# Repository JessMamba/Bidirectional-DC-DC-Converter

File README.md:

# Three-Stage Cubic Bidirectional DC-DC Converter for Renewable Energy & Battery Storage Systems

A high-gain, non-isolated, high-efficiency **Three-Stage Cubic Bidirectional DC-DC Converter** designed for renewable energy systems, battery energy storage systems (BESS), and electric vehicle (EV) microgrid interfaces (V2G/G2V). 

This repository contains full theoretical derivations (CCM/DCM), circuit parameter calculations, 3D MATLAB optimization surface scripts, mode-dependent closed-loop PID controller designs, PSCAD simulation models, and KiCad PCB designs/Gerber files with hardware prototype implementation details.

---

## 📌 Table of Contents
- [1. Executive Summary](#1-executive-summary)
- [2. Key Features & Specifications](#2-key-features--specifications)
- [3. Converter Topology & Operating Principles](#3-converter-topology--operating-principles)
  - [3.1 Step-Up (Boost) Mode](#31-step-up-boost-mode)
  - [3.2 Step-Down (Buck) Mode](#32-step-down-buck-mode)
- [4. Mathematical Modeling & Component Calculations](#4-mathematical-modeling--component-calculations)
  - [4.1 Voltage Gain Expressions](#41-voltage-gain-expressions)
  - [4.2 Inductor & Capacitor Dimensioning](#42-inductor--capacitor-dimensioning)
  - [4.3 Switch Voltage and Current Stress Analysis](#43-switch-voltage-and-current-stress-analysis)
  - [4.4 Comparative Analysis](#44-comparative-analysis)
- [5. Mode-Dependent Closed-Loop PID Controller Design](#5-mode-dependent-closed-loop-pid-controller-design)
  - [5.1 Buck Mode Controller](#51-buck-mode-controller)
  - [5.2 Boost Mode Controller](#52-boost-mode-controller)
  - [5.3 MATLAB Closed-Loop Verification](#53-matlab-closed-loop-verification)
- [6. PSCAD Simulation & Results](#6-pscad-simulation--results)
- [7. Hardware Bill of Materials (BOM)](#7-hardware-bill-of-materials-bom)
- [8. PCB Design & Hardware Implementation](#8-pcb-design--hardware-implementation)
- [9. Repository Structure](#9-repository-structure)
- [10. References](#10-references)

---

## 1. Executive Summary

Conventional boost and buck converters suffer from extreme duty cycle requirements, excessive semiconductor stress, and sharp efficiency degradation when operating at large voltage conversion ratios. To eliminate these constraints, this project proposes a **Three-Stage Cubic Bidirectional DC-DC Converter**. 

By leveraging a cubic voltage transfer ratio ($M_{	ext{Boost}} = rac{1}{(1-D)^3}$ and $M_{	ext{Buck}} = D^3$), the converter achieves a wide voltage conversion range (**24V DC $\leftrightarrow$ 300V DC**) at moderate duty cycles ($D_{	ext{Boost}} = 0.57$, $D_{	ext{Buck}} = 0.43$) while maintaining lower voltage and current stresses on power MOSFETs. The topology utilizes **6 MOSFET switches, 4 capacitors, and 3 inductors**, achieving a calculated peak efficiency of **94.16%** due to reduced switching losses (only 1 or 2 switches actively triggered in each sub-interval).

---

## 2. Key Features & Specifications

| Parameter | Symbol | Nominal Value | Unit |
| :--- | :--- | :--- | :--- |
| **Rated Power** | $P_{o}$ | **900** | W |
| **Low Voltage Side (LV)** | $V_{LV}$ | **24** | V |
| **High Voltage Side (HV)** | $V_{HV}$ | **300** | V |
| **Switching Frequency** | $f_s$ | **50** | kHz |
| **Peak Efficiency** | $\eta_{	ext{peak}}$ | **94.16** | % |
| **Boost Duty Cycle ($24	ext{V}	o300	ext{V}$)** | $D_{	ext{boost}}$ | **0.5703** | - |
| **Buck Duty Cycle ($300	ext{V}	o24	ext{V}$)** | $D_{	ext{buck}}$ | **0.4305** | - |
| **Maximum Duty Cycle Limit** | $D_{	ext{max}}$ | **0.90** | - |
| **Ground Topology** | - | **Common Ground** | - |

---

## 3. Converter Topology & Operating Principles

The converter consists of three energy storage inductors ($L_1, L_2, L_3$), two intermediate energy transfer capacitors ($C_1, C_2$), input/output filtering capacitors ($C_L, C_H$), and 6 MOSFET switches ($S_1, S_2, S_3, S_4, S_5, S_6$) configured for bidirectional power flow.

```
                  +--------------------[ S1 ]-------------------+
                  |                                             |
                  |          S2                     S3          |
  [LV Input] -----+---(L1)---[--]---+---(L2)---[--]----+        |
  (24V DC)        |                 |                  |        |
                  |                --- C1             --- C2    |
                 --- CL            ---                ---       |
                 ---                |                  |        |
                  |                GND         [S4]----+---(L3)-+---[S6]---+--- [HV Output]
                  |                             |               |          |    (300V DC)
                  |                            GND             [S5]       --- CH
                  |                                             |         ---
                  +---------------------------------------------+----------+--- GND
```

### 3.1 Step-Up (Boost) Mode
Energy flows from Low Voltage ($V_{LV} = 24	ext{V}$) to High Voltage ($V_{HV} = 300	ext{V}$).
- **State 1 ($0 \le t < D T_s$):** Switches $S_1, S_4, S_5$ are ON; body diodes $D_1, D_2, D_3$ are reverse-biased. $L_1$ is magnetized by $V_{LV}$, while $L_2$ and $L_3$ are magnetized by intermediate capacitors $C_1$ and $C_2$. All inductor currents increase linearly.
- **State 2 ($D T_s \le t < T_s$):** Switches $S_1, S_4, S_5$ are OFF; body diodes $D_1, D_2, D_3$ conduct. Stored energy is transferred forward: $L_1$ charges $C_1$, $L_2$ charges $C_2$, and $L_3$ feeds the HV load and output filtering capacitor $C_H$.

### 3.2 Step-Down (Buck) Mode
Energy flows from High Voltage ($V_{HV} = 300	ext{V}$) to Low Voltage ($V_{LV} = 24	ext{V}$).
- **State 1 ($0 \le t < D T_s$):** Switches $S_2, S_3, S_6$ are ON. $L_3$ is energized by $V_{HV}$, and $L_2, L_1$ are energized by intermediate capacitors $C_2, C_1$. Inductor currents ramp up linearly.
- **State 2 ($D T_s \le t < T_s$):** Switches $S_2, S_3, S_6$ are OFF; body diodes $D_1, D_4, D_5$ conduct. Energy is demagnetized toward the LV side: $L_3 	o C_2$, $L_2 	o C_1$, and $L_1 	o R_{	ext{load}}$ (LV side).

---

## 4. Mathematical Modeling & Component Calculations

### 4.1 Voltage Gain Expressions

#### Continuous Conduction Mode (CCM)
- **Intermediate Capacitor Voltages (Boost):**
  $$V_{C1} = rac{V_{LV}}{1-D}, \quad V_{C2} = rac{V_{LV}}{(1-D)^2}$$
- **Intermediate Capacitor Voltages (Buck):**
  $$V_{C2} = D \cdot V_{HV}, \quad V_{C1} = D^2 \cdot V_{HV}$$
- **Cubic Voltage Transfer Ratio (VTR):**
  $$M_{	ext{CCM, Step-Up}} = rac{V_{HV}}{V_{LV}} = rac{1}{(1-D)^3}$$
  $$M_{	ext{CCM, Step-Down}} = rac{V_{LV}}{V_{HV}} = D^3$$

#### Discontinuous Conduction Mode (DCM)
- **Step-Up Mode DCM Gain:**
  $$M_{	ext{DCM, Step-Up}} = rac{V_{HV}}{V_{LV}} = rac{(D+D_1)(D+D_2)(D+D_3)}{D_1 (D D_2 + D_2 D_3 - D D_3)}$$
- **Step-Down Mode DCM Gain:**
  $$M_{	ext{DCM, Step-Down}} = rac{V_{LV}}{V_{HV}} = rac{D^2 (D + D_3 - D_2)}{(D + D_1)(D + D_2)(D + D_3)}$$

### 4.2 Inductor & Capacitor Dimensioning

Inductances and capacitances are dimensioned analytically to ensure robust CCM operation with current and voltage ripple $<1\%$:

$$L_1 \ge rac{D_{	ext{boost}} V_{LV}}{\Delta i_{L1} f_s}, \quad L_2 \ge rac{D_{	ext{boost}} V_{LV}}{(1-D_{	ext{boost}}) \Delta i_{L2} f_s}, \quad L_3 \ge rac{D_{	ext{boost}} V_{LV}}{(1-D_{	ext{boost}})^2 \Delta i_{L3} f_s}$$

| Component | Minimum Calculated (Boost) | Minimum Calculated (Buck) | Selected Hardware Value |
| :--- | :--- | :--- | :--- |
| **Inductor $L_1$** | $0.3898	ext{ mH}$ | $0.2282	ext{ mH}$ | **$330\ \mu	ext{H}$ / High Current Toroid** |
| **Inductor $L_2$** | $0.7418	ext{ mH}$ | $0.5940	ext{ mH}$ | **$330\ \mu	ext{H}$ / High Current Toroid** |
| **Inductor $L_3$** | $1.1200	ext{ mH}$ | $1.1390	ext{ mH}$ | **$330\ \mu	ext{H}$ / High Current Toroid** |
| **Capacitor $C_1$** | $9.221\ \mu	ext{F}$ | $9.018\ \mu	ext{F}$ | **$110\ \mu	ext{F}$ / 100V Electrolytic** |
| **Capacitor $C_2$** | $9.518\ \mu	ext{F}$ | $9.225\ \mu	ext{F}$ | **$110\ \mu	ext{F}$ / 250V Electrolytic** |
| **Filtering $C_H$** | $4.276\ \mu	ext{F}$ | $1.460\ \mu	ext{F}$ | **$470\ \mu	ext{F}$ / 500V Electrolytic** |
| **Filtering $C_L$** | $25.10\ \mu	ext{F}$ | $7.726\ \mu	ext{F}$ | **$470\ \mu	ext{F}$ / 100V Electrolytic** |

---

### 4.3 Switch Voltage and Current Stress Analysis

Total Voltage Stress (TVS) and Total Current Stress (TCS) are minimized due to intermediate stage capacitor sharing:
$$	ext{TVS} = 3 V_{HV}, \quad 	ext{TCS} = 3 I_{LV}$$

- **High Voltage Switches ($S_1, S_5, S_6$):** Block full output voltage $V_{HV}  pprox 300	ext{V}$. Selected: **SRC65R032FB Super-Junction MOSFETs (650V, 88A, $R_{DS(on)} = 32	ext{m}\Omega$)**.
- **Intermediate Stage Switches ($S_2, S_3, S_4$):** Block reduced stage voltages ($V_{C1}, V_{C2}$). Selected: **IRFP4227PBF Power MOSFETs (200V, 65A, $R_{DS(on)} = 21	ext{m}\Omega$)**.

---

### 4.4 Comparative Analysis

| Feature / Topology | Ref [1] | Ref [2] | Ref [3] | Ref [4] | **Proposed Converter** |
| :--- | :--- | :--- | :--- | :--- | :--- |
| **Element Count ($S-C-L$)** | $4-1-2$ | $4-2-2$ | $5-3-2$ | $4-3-1$ | **$6-4-3$** |
| **Step-Down Gain** | $D$ | $D/4$ | $D/2$ | $D^2$ | **$D^3$ (Cubic)** |
| **Step-Up Gain** | $rac{1}{1-D}$ | $rac{4}{1-D}$ | $rac{2}{1-D}$ | $rac{1}{(1-D)^2}$ | **$rac{1}{(1-D)^3}$ (Cubic)** |
| **Common Ground** | Yes | Yes | No | Yes | **Yes** |
| **Rated Power [W]** | $500$ | $500$ | $500$ | $1000$ | **$900$** |
| **Switching Freq. [kHz]** | $50$ | $100$ | $50$ | $50$ | **$50$** |
| **Peak Efficiency [%]** | $95.8\%$ | $96.0\%$ | $95.6\%$ | $96.8\%$ | **$94.16\%$** |

---

## 5. Mode-Dependent Closed-Loop PID Controller Design

Since the open-loop transient response exhibits significant overshoot (>135% in Buck, ~48.6% in Boost) and steady-state error, a **Mode-Dependent PID Control Strategy** is implemented with distinct coefficients for Buck and Boost operations.

### 5.1 Buck Mode Controller
- **Plant Transfer Function (Open-Loop Approx.):**
  $$G_{p,	ext{Buck}}(s) = rac{7.90 	imes 10^6}{s^2 + 1158 s + 8.32 	imes 10^6}$$
- **Target Specs:** Overshoot $M_p \le 5\%$, Settling Time $t_s \le 7	ext{ ms}$, $\zeta_d = 0.69$, $\omega_{n,d} = 828	ext{ rad/s}$. Third pole $p_3 = 8280	ext{ rad/s}$.
- **PID Parameters:**
  $$K_{p,	ext{Buck}} = 0.2312, \quad K_{i,	ext{Buck}} = 718.56, \quad K_{d,	ext{Buck}} = 0.001046$$

### 5.2 Boost Mode Controller
- **Plant Transfer Function (Open-Loop Approx.):**
  $$G_{p,	ext{Boost}}(s) = rac{16781.4}{s^2 + 57.73 s + 16624.5}$$
- **Target Specs:** Overshoot $M_p \le 5\%$, Settling Time $t_s \le 50	ext{ ms}$, $\zeta_d = 0.69$, $\omega_{n,d} = 115.94	ext{ rad/s}$. Third pole $p_3 = 579.71	ext{ rad/s}$.
- **PID Parameters:**
  $$K_{p,	ext{Boost}} = 5.338, \quad K_{i,	ext{Boost}} = 464.37, \quad K_{d,	ext{Boost}} = 0.04064$$

### 5.3 MATLAB Closed-Loop Verification

| Metric | Buck Open-Loop | Buck PID Closed-Loop | Boost Open-Loop | Boost PID Closed-Loop |
| :--- | :--- | :--- | :--- | :--- |
| **Reference Voltage** | $24.0	ext{V}$ | **$24.000	ext{V}$** | $300.0	ext{V}$ | **$300.000	ext{V}$** |
| **Peak Voltage** | $54.11	ext{V}$ | **$24.61	ext{V}$** | $453.28	ext{V}$ | **$307.44	ext{V}$** |
| **Maximum Overshoot**| $135.5\%$ | **$2.56\%$** | $48.6\%$ | **$2.48\%$** |
| **Settling Time ($t_s, 2\%$)**| $6.9	ext{ ms}$ | **$7.69	ext{ ms}$** | $138.6	ext{ ms}$ | **$33.87	ext{ ms}$** |
| **Steady-State Error** | $1.236	ext{V}$ (5.15%) | **$ pprox 0	ext{V}$** | $-2.832	ext{V}$ (0.94%)| **$ pprox 0	ext{V}$** |

---

## 6. PSCAD Simulation & Results

Full switching circuit topologies for both **Boost** ($24	ext{V} 	o 300	ext{V}$, $D=0.57$) and **Buck** ($300	ext{V} 	o 24	ext{V}$, $D=0.43$) were modeled in PSCAD.

Key simulation highlights:
1. **Continuous Conduction Mode (CCM):** Inductor currents $I_{L1}, I_{L2}, I_{L3}$ remain strictly positive across all switching cycles without reaching zero.
2. **Capacitor Voltage Stresses:** Intermediate capacitor voltages $V_{C1}$ and $V_{C2}$ align perfectly with quadratic/linear theoretical derivations ($V_{C1}=54	ext{V}$, $V_{C2}=127	ext{V}$).
3. **MOSFET Voltage Blocking:** High-side switches ($S_1, S_5, S_6$) reliably block $300	ext{V}$ peak DC line voltage, whereas intermediate stage switches ($S_2, S_3, S_4$) operate under reduced stress ($<135	ext{V}$).

---

## 7. Hardware Bill of Materials (BOM)

| Designator | Component / Part | Specification / Value | Package | Manufacturer / Link |
| :--- | :--- | :--- | :--- | :--- |
| **Q1, Q5, Q6** | SRC65R032FB | Super-Junction N-Ch MOSFET (650V, 88A, $32	ext{m}\Omega$) | TO-247 | [Datasheet Link](https://www.ulutaselektronik.com/urun/src65r032fb-32m-88a-650v-super-junction-n-channel-power-mosfet) |
| **Q2, Q3, Q4** | IRFP4227PBF | Power N-Ch MOSFET (200V, 65A, $21	ext{m}\Omega$) | TO-247 | [Datasheet Link](https://www.ulutaselektronik.com/urun/irfp4227pbf-to-247-65a-200v-mosfet) |
| **L1, L2, L3** | Custom Toroidal Inductors | $330\ \mu	ext{H}$, High Current Ferrite Core | Radial | Custom Wound |
| **C1, C2** | Electrolytic Capacitors | $110\ \mu	ext{F}$ / 100V & 250V | Radial | Standard Industrial |
| **CL, CH** | Filtering Capacitors | $470\ \mu	ext{F}$ / 100V & 500V | Radial | Standard Industrial |
| **J1-J16** | High Current Screw Terminals | 2-Pin Screw Terminal Connectors | 5.08mm Pitch | Standard |

---

## 8. PCB Design & Hardware Implementation

The hardware prototype was designed using **KiCad Electronic Design Suite**, obeying high-frequency power electronics layout rules:
- **Loop Area Minimization:** Reduced parasitic trace inductance to suppress voltage spikes across switch nodes.
- **Thermal & Current Routing:** Heavy copper pours on power traces to withstand currents up to $22.3	ext{A}$.
- **PCB Fabrication Cost:** Gerber files optimized and manufactured at industrial standards ($15/board).
- **Physical Assembly:** Components hand-soldered in the Electrical & Electronics Engineering Laboratory at Bursa Technical University.

---

## 9. Repository Structure

```
├── docs/
│   ├── Bidirectional_DC_DC_Converter_Project_Report.pdf  # Full Turkish Graduation Project Report
│   └── PCB_Schematics_and_3D_Render.png                  # KiCad 3D layout views
├── hardware/
│   ├── KiCad_Project/                                    # KiCad Schematics & PCB layout files
│   ├── Gerbers/                                          # Production-ready Gerber manufacturing files
│   └── BOM.csv                                           # Bill of Materials
├── matlab/
│   ├── passive_components_3d_surfaces.m                  # 3D parameter optimization scripts
│   ├── PID_Buck_ClosedLoop.m                             # Buck mode PID verification script
│   └── PID_Boost_ClosedLoop.m                            # Boost mode PID verification script
├── simulation/
│   ├── PSCAD_Boost_Circuit.pscx                          # PSCAD Boost mode simulation model
│   └── PSCAD_Buck_Circuit.pscx                           # PSCAD Buck mode simulation model
├── LICENSE                                               # MIT License
└── README.md                                             # Project README file
```

---

## 10. References

1. S. Sarani and X. Liang, "Non-Isolated High Voltage Gain Bidirectional DC-DC Converters: A Review," in *Proceedings of the IEEE Industry Applications Society Annual Meeting (IAS)*, 2024, pp. 1-7, doi: [10.1109/IAS55788.2024.11023749](https://doi.org/10.1109/IAS55788.2024.11023749).
2. K. Zhou, K. Xu, and Y. Sun, "Bidirectional DC/DC Converter Based on Interleaved Parallel Buck/Boost Cascades CLLLC," *International Journal of Circuit Theory and Applications*, vol. 53, no. 8, pp. 4455-4474, 2025, doi: [10.1002/cta.4363](https://doi.org/10.1002/cta.4363).
3. M. T. Talluri and V. Karthikeyan, "Regenerative Switched-Inductor/Capacitor Configuration-Based Cubic Bidirectional DC-DC Converter for EV Applications," *IEEE Journal of Emerging and Selected Topics in Industrial Electronics*, early access, 2025, doi: [10.1109/JESTIE.2025.3607163](https://doi.org/10.1109/JESTIE.2025.3607163).
4. R. Kallelapu, S. Peddapati, and S. V. K. Naresh, "A Family of Non-Isolated Quadratic Buck-Boost Bidirectional Converters With Reduced Current Ripple for EV Charger Applications," *IEEE Transactions on Power Electronics*, early access, 2025, doi: [10.1109/TPEL.2025.3592387](https://doi.org/10.1109/TPEL.2025.3592387).

---
*Developed as a Senior Capstone Project at Bursa Technical University, Department of Electrical & Electronics Engineering.*

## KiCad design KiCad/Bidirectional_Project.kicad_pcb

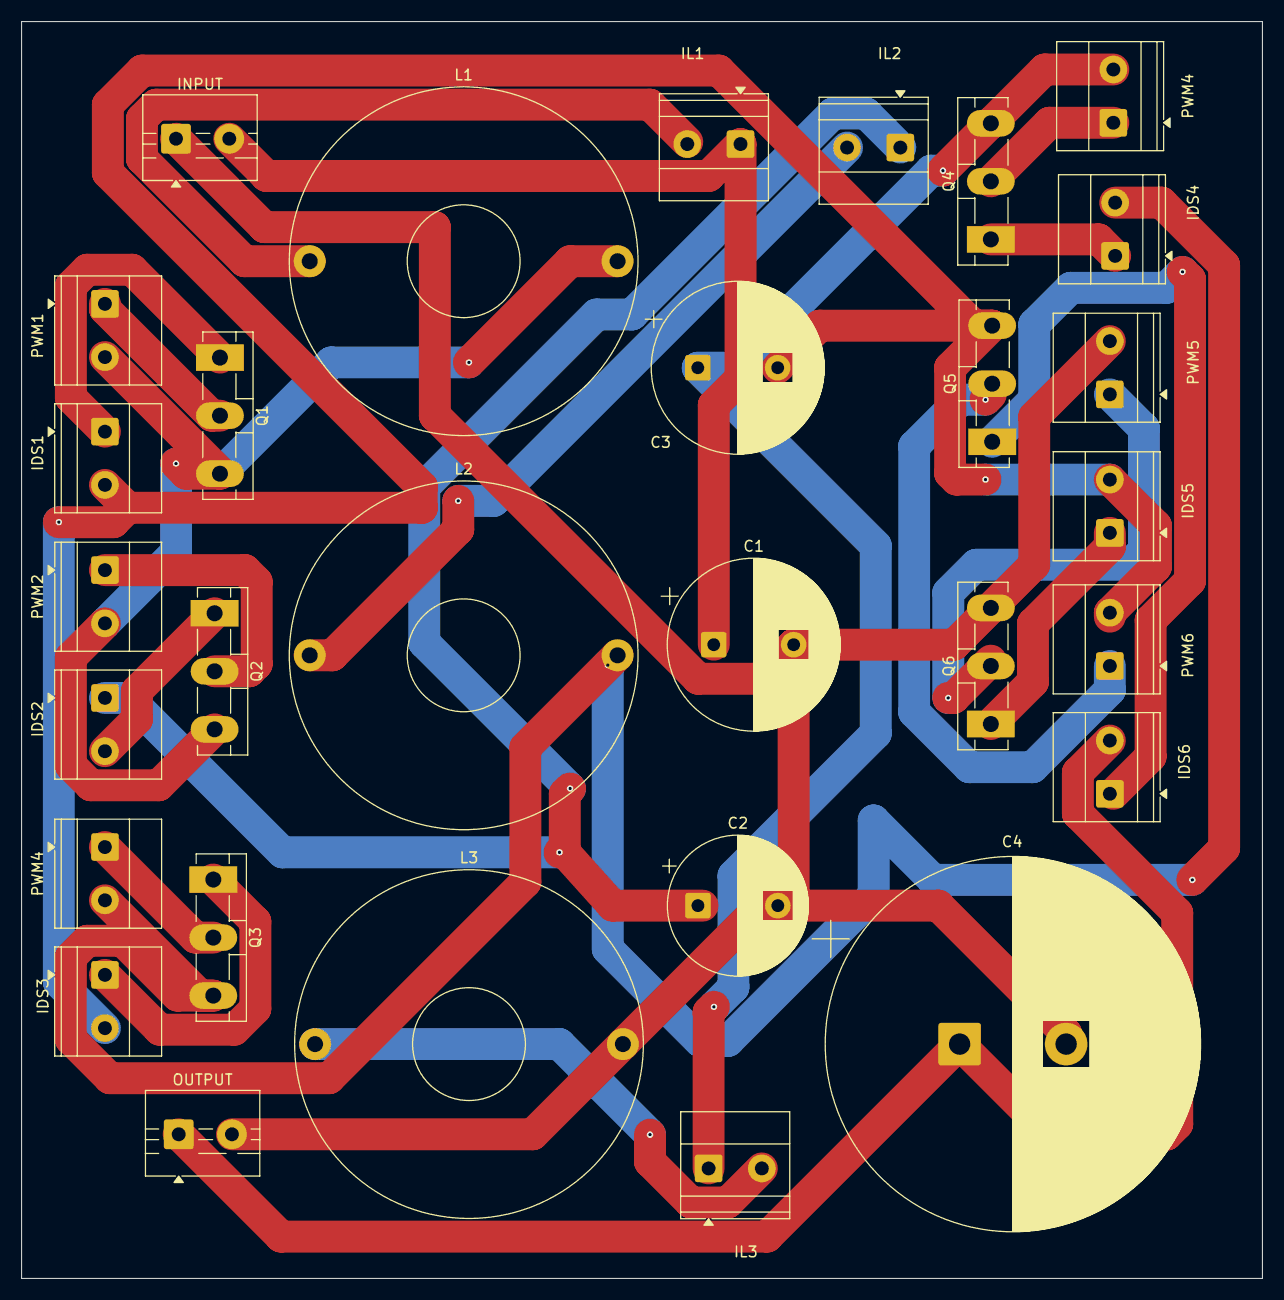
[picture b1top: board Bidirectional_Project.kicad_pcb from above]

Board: 2 copper layers, 116.5 x 118.0 mm, 30 parts (0 on the bottom side), 23 nets.

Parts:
C1: 470u; CP_Radial_D16.0mm_P7.50mm
C2: 110u; CP_Radial_D13.0mm_P7.50mm
C3: 110u; CP_Radial_D16.0mm_P7.50mm
C4: 470u; CP_Radial_D35.0mm_P10.00mm_SnapIn
IDS1: IDS1; TerminalBlock_Phoenix_MKDS-1,5-2_1x02_P5.00mm_Horizontal
IDS2: IDS2; TerminalBlock_Phoenix_MKDS-1,5-2_1x02_P5.00mm_Horizontal
IDS3: IDS3; TerminalBlock_Phoenix_MKDS-1,5-2_1x02_P5.00mm_Horizontal
IDS4: IDS4; TerminalBlock_Phoenix_MKDS-1,5-2_1x02_P5.00mm_Horizontal
IDS5: IDS5; TerminalBlock_Phoenix_MKDS-1,5-2_1x02_P5.00mm_Horizontal
IDS6: IDS6; TerminalBlock_Phoenix_MKDS-1,5-2_1x02_P5.00mm_Horizontal
IL1: IL1; TerminalBlock_Phoenix_MKDS-1,5-2_1x02_P5.00mm_Horizontal
IL2: IL2; TerminalBlock_Phoenix_MKDS-1,5-2_1x02_P5.00mm_Horizontal
IL3: IL3; TerminalBlock_Phoenix_MKDS-1,5-2_1x02_P5.00mm_Horizontal
INPUT: Conn_01x02_Socket; TerminalBlock_MaiXu_MX126-5.0-02P_1x02_P5.00mm
L1: 750; L_Toroid_Horizontal_D32.5mm_P28.90mm_Bourns_2300
L2, L3: 330; L_Toroid_Horizontal_D32.5mm_P28.90mm_Bourns_2300
OUTPUT: Conn_01x02_Socket; TerminalBlock_MaiXu_MX126-5.0-02P_1x02_P5.00mm
PWM1: PWM1; TerminalBlock_Phoenix_MKDS-1,5-2_1x02_P5.00mm_Horizontal
PWM2: PWM2; TerminalBlock_Phoenix_MKDS-1,5-2_1x02_P5.00mm_Horizontal
PWM4: PWM3; TerminalBlock_Phoenix_MKDS-1,5-2_1x02_P5.00mm_Horizontal
PWM4#2: PWN4; TerminalBlock_Phoenix_MKDS-1,5-2_1x02_P5.00mm_Horizontal
PWM5: PWM5; TerminalBlock_Phoenix_MKDS-1,5-2_1x02_P5.00mm_Horizontal
PWM6: PWM6; TerminalBlock_Phoenix_MKDS-1,5-2_1x02_P5.00mm_Horizontal
Q1, Q2, Q3, Q4, Q5, Q6: NMOS; TO-3P-3_Vertical

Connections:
GND: C1.2, C2.2, C4.2, INPUT.1, L3.2, OUTPUT.2, PWM5.2, Q6.3 (S)
unnamed: C1.1, IL1.1, INPUT.2
unnamed: PWM2.1, Q2.2 (G)
unnamed: PWM4.1, Q3.2 (G)
unnamed: IL2.2, L2.1
unnamed: PWM4#2.1, Q4.2 (G)
unnamed: C3.1, IL3.1, PWM4#2.2, Q4.3 (S)
unnamed: PWM5.1, Q6.2 (G)
unnamed: IL3.2, L3.1
unnamed: PWM6.1, Q5.2 (G)
unnamed: IL1.2, L1.1
unnamed: IDS1.1, Q1.1 (D)
unnamed: C3.2, IDS1.2, IDS3.2, IDS5.2, PWM6.2, Q5.3 (S)
unnamed: PWM1.1, Q1.2 (G)
unnamed: L1.2, PWM1.2, PWM2.2, Q1.3 (S), Q2.3 (S)
unnamed: C2.1, IDS2.1, IL2.1
unnamed: IDS2.2, Q2.1 (D)
unnamed: IDS3.1, Q3.1 (D)
unnamed: IDS4.1, Q4.1 (D)
unnamed: IDS4.2, L2.2, PWM4.2, Q3.3 (S)
unnamed: IDS6.1, Q5.1 (D)
unnamed: C4.1, IDS6.2, OUTPUT.1
unnamed: IDS5.1, Q6.1 (D)
